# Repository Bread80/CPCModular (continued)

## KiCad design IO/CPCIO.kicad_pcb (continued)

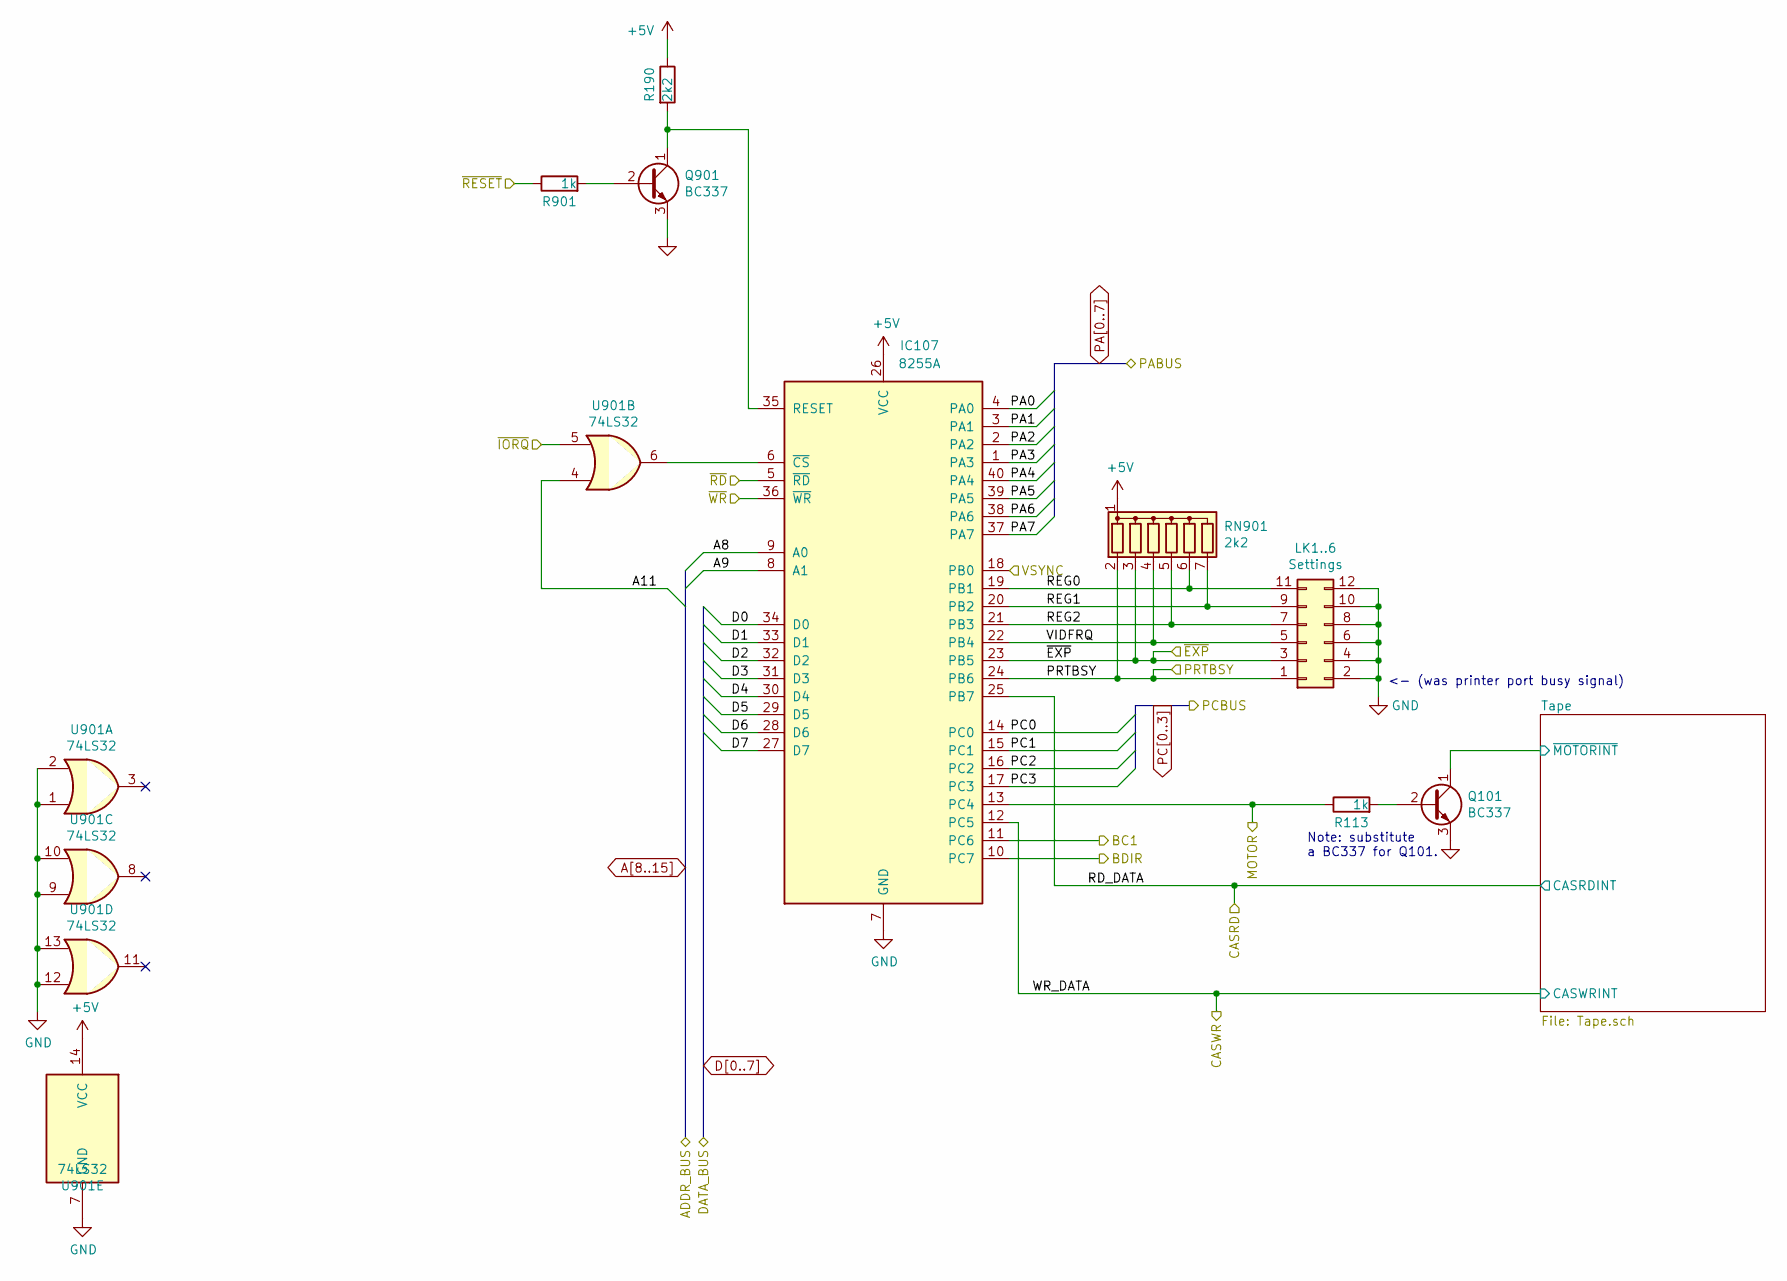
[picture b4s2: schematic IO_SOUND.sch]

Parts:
IC107: 8255A; DIP-40_W15.24mm_Socket
LK1..6: Settings; PinHeader_2x06_P2.54mm_Vertical
Q101, Q901: BC337; TO-92_HandSolder
R113, R901: 1k; R_Axial_DIN0207_L6.3mm_D2.5mm_P7.62mm_Horizontal
R190: 2k2; R_Axial_DIN0207_L6.3mm_D2.5mm_P7.62mm_Horizontal
RN901: 2k2; R_Array_SIP7
U901: 74LS32; DIP-14_W7.62mm_Socket

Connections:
+5V: IC107.26 (VCC), R190.1, RN901.1 (common), U901.14 (VCC); also elsewhere on the board
/IO_SOUND/BC1: IC107.11 (PC6); also elsewhere on the board
/IO_SOUND/BDIR: IC107.10 (PC7); also elsewhere on the board
/IO_SOUND/CASRD: IC107.25 (PB7); also elsewhere on the board
/IO_SOUND/CASWR: IC107.12 (PC5); also elsewhere on the board
/IO_SOUND/MOTOR: IC107.13 (PC4), R113.1; also elsewhere on the board
/IO_SOUND/PRTBSY: IC107.24 (PB6), LK1..6.1, RN901.2 (R1); also elsewhere on the board
/IO_SOUND/REG0: IC107.19 (PB1), LK1..6.11, RN901.6 (R5)
/IO_SOUND/REG1: IC107.20 (PB2), LK1..6.9, RN901.7 (R6)
/IO_SOUND/REG2: IC107.21 (PB3), LK1..6.7, RN901.5 (R4)
/IO_SOUND/Tape/~MOTORINT: Q101.1 (C); also elsewhere on the board
/IO_SOUND/VIDFRQ: IC107.22 (PB4), LK1..6.5, RN901.4 (R3)
/IO_SOUND/VSYNC: IC107.18 (PB0); also elsewhere on the board
/IO_SOUND/~EXP: IC107.23 (PB5), LK1..6.3, RN901.3 (R2); also elsewhere on the board
/IO_SOUND/~IORQ: U901.5; also elsewhere on the board
/IO_SOUND/~RD: IC107.5 (~RD~); also elsewhere on the board
/IO_SOUND/~RESET: R901.1; also elsewhere on the board
/IO_SOUND/~WR: IC107.36 (~WR~); also elsewhere on the board
A8: IC107.9 (A0); also elsewhere on the board
A9: IC107.8 (A1); also elsewhere on the board
A11: U901.4; also elsewhere on the board
D0: IC107.34 (D0); also elsewhere on the board
D1: IC107.33 (D1); also elsewhere on the board
D2: IC107.32 (D2); also elsewhere on the board
D3: IC107.31 (D3); also elsewhere on the board
D4: IC107.30 (D4); also elsewhere on the board
D5: IC107.29 (D5); also elsewhere on the board
D6: IC107.28 (D6); also elsewhere on the board
D7: IC107.27 (D7); also elsewhere on the board
GND: IC107.7 (GND), LK1..6.2, LK1..6.4, LK1..6.6, LK1..6.8, LK1..6.10, LK1..6.12, Q101.3 (E), Q901.3 (E), U901.1, U901.2, U901.7 (GND), U901.9, U901.10, U901.12, U901.13; also elsewhere on the board
unnamed: IC107.6 (~CS~), U901.6
unnamed: IC107.35 (RESET), Q901.1 (C), R190.2
unnamed: Q101.2 (B), R113.2
unnamed: Q901.2 (B), R901.2
PA0: IC107.4 (PA0); also elsewhere on the board
PA1: IC107.3 (PA1); also elsewhere on the board
PA2: IC107.2 (PA2); also elsewhere on the board
PA3: IC107.1 (PA3); also elsewhere on the board
PA4: IC107.40 (PA4); also elsewhere on the board
PA5: IC107.39 (PA5); also elsewhere on the board
PA6: IC107.38 (PA6); also elsewhere on the board
PA7: IC107.37 (PA7); also elsewhere on the board
PC0: IC107.14 (PC0); also elsewhere on the board
PC1: IC107.15 (PC1); also elsewhere on the board
PC2: IC107.16 (PC2); also elsewhere on the board
PC3: IC107.17 (PC3); also elsewhere on the board

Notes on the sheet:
Note: substitute a BC337 for Q101.
<- (was printer port busy signal)

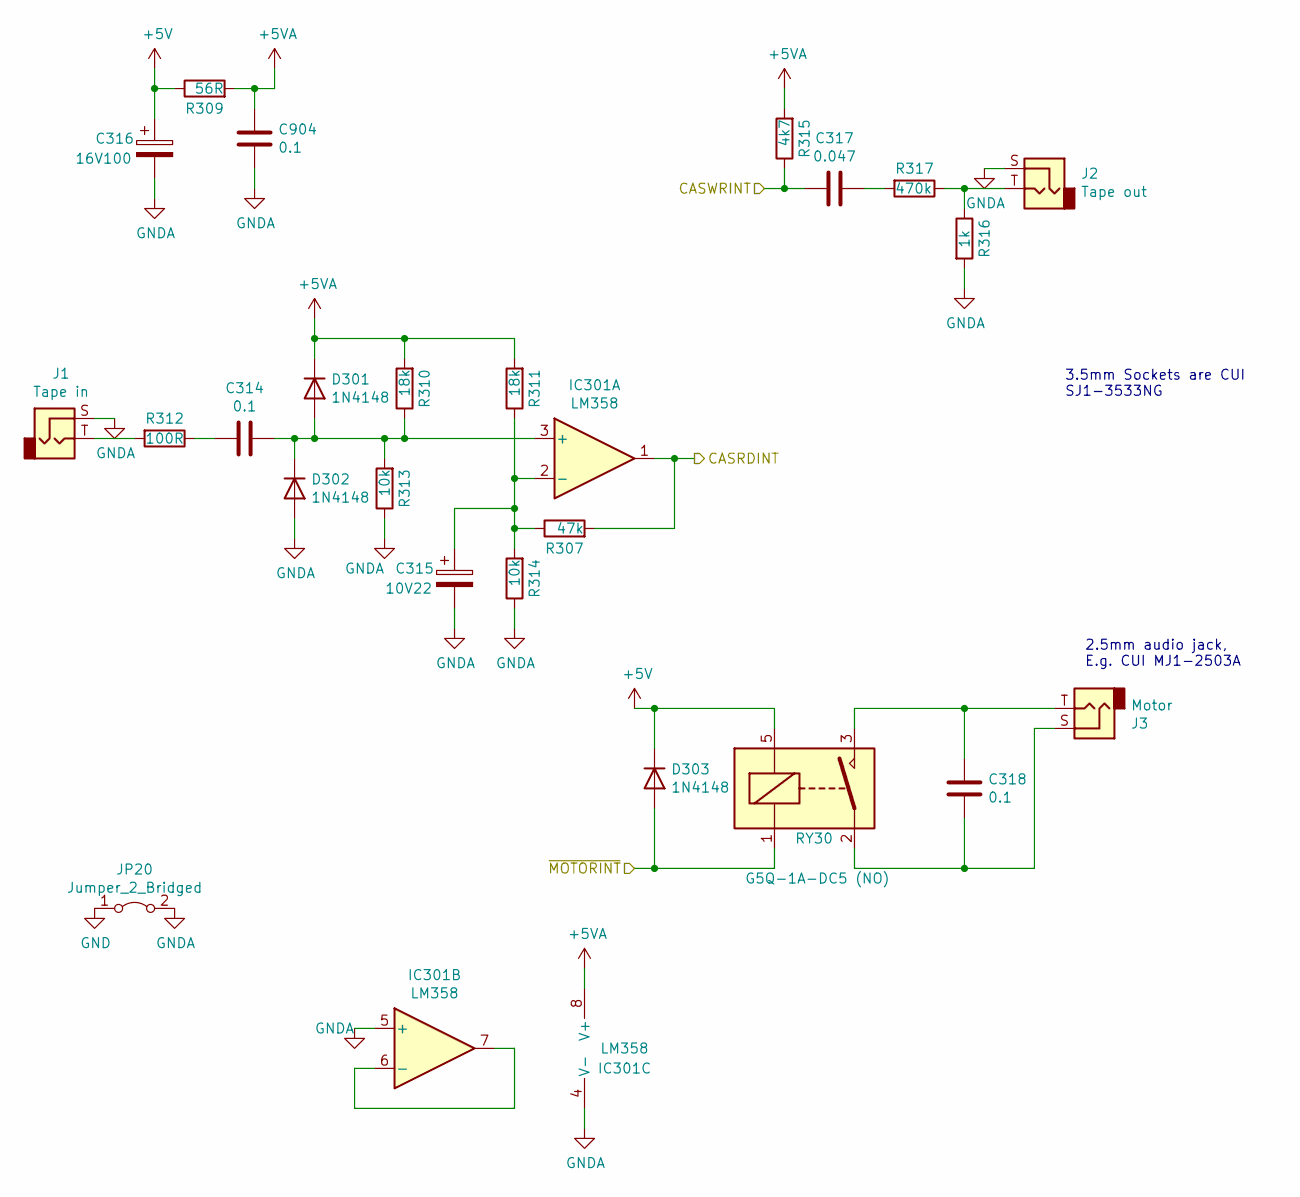
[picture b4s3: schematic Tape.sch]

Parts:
C314, C318, C904: 0.1; C_Disc_D3.0mm_W2.0mm_P2.50mm
C315: 10V22; CP_Radial_D6.3mm_P2.50mm
C316: 16V100; CP_Radial_D6.3mm_P2.50mm
C317: 0.047; C_Disc_D3.0mm_W2.0mm_P2.50mm
D301, D302, D303: 1N4148; D_DO-35_SOD27_P7.62mm_Horizontal
IC301: LM358; DIP-8_W7.62mm_Socket
J1: Tape in; Jack_3.5mm_CUI_SJ1-3533NG_Horizontal
J2: Tape out; Jack_3.5mm_CUI_SJ1-3533NG_Horizontal
J3: Motor; CUI_MJ1_2503A
JP20: Jumper_2_Bridged; NetTie-2_SMD_Pad0.5mm
R307: 47k; R_Axial_DIN0207_L6.3mm_D2.5mm_P7.62mm_Horizontal
R309: 56R; R_Axial_DIN0207_L6.3mm_D2.5mm_P7.62mm_Horizontal
R310, R311: 18k; R_Axial_DIN0207_L6.3mm_D2.5mm_P7.62mm_Horizontal
R312: 100R; R_Axial_DIN0207_L6.3mm_D2.5mm_P7.62mm_Horizontal
R313, R314: 10k; R_Axial_DIN0207_L6.3mm_D2.5mm_P7.62mm_Horizontal
R315: 4k7; R_Axial_DIN0207_L6.3mm_D2.5mm_P7.62mm_Horizontal
R316: 1k; R_Axial_DIN0207_L6.3mm_D2.5mm_P7.62mm_Horizontal
R317: 470k; R_Axial_DIN0207_L6.3mm_D2.5mm_P7.62mm_Horizontal
RY30: G5Q-1A-DC5 (NO); Relay_SPST_Omron-G5Q-1A

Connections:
+5V: C316.1, D303.1 (K), R309.1, RY30.5; also elsewhere on the board
+5VA: C904.1, D301.1 (K), IC301.8 (V+), R309.2, R310.2, R311.2, R315.2
/IO_SOUND/CASRD: IC301.1, R307.2; also elsewhere on the board
/IO_SOUND/CASWR: C317.2, R315.1; also elsewhere on the board
/IO_SOUND/Tape/~MOTORINT: D303.2 (A), RY30.1; also elsewhere on the board
GND: JP20.1 (A); also elsewhere on the board
GNDA: C315.2, C316.2, C904.2, D302.2 (A), IC301.4 (V-), IC301.5 (+), J1.S, J2.S, JP20.2 (B), R313.1, R314.1, R316.2
unnamed: C314.1, D301.2 (A), D302.1 (K), IC301.3 (+), R310.1, R313.2
unnamed: C314.2, R312.1
unnamed: C315.1, IC301.2 (-), R307.1, R311.1, R314.2
unnamed: C317.1, R317.2
unnamed: C318.1, J3.T, RY30.3
unnamed: C318.2, J3.S, RY30.2
unnamed: IC301.6 (-), IC301.7
unnamed: J1.T, R312.2
unnamed: J2.T, R316.1, R317.1

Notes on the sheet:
3.5mm Sockets are CUI SJ1-3533NG
2.5mm audio jack, E.g. CUI MJ1-2503A

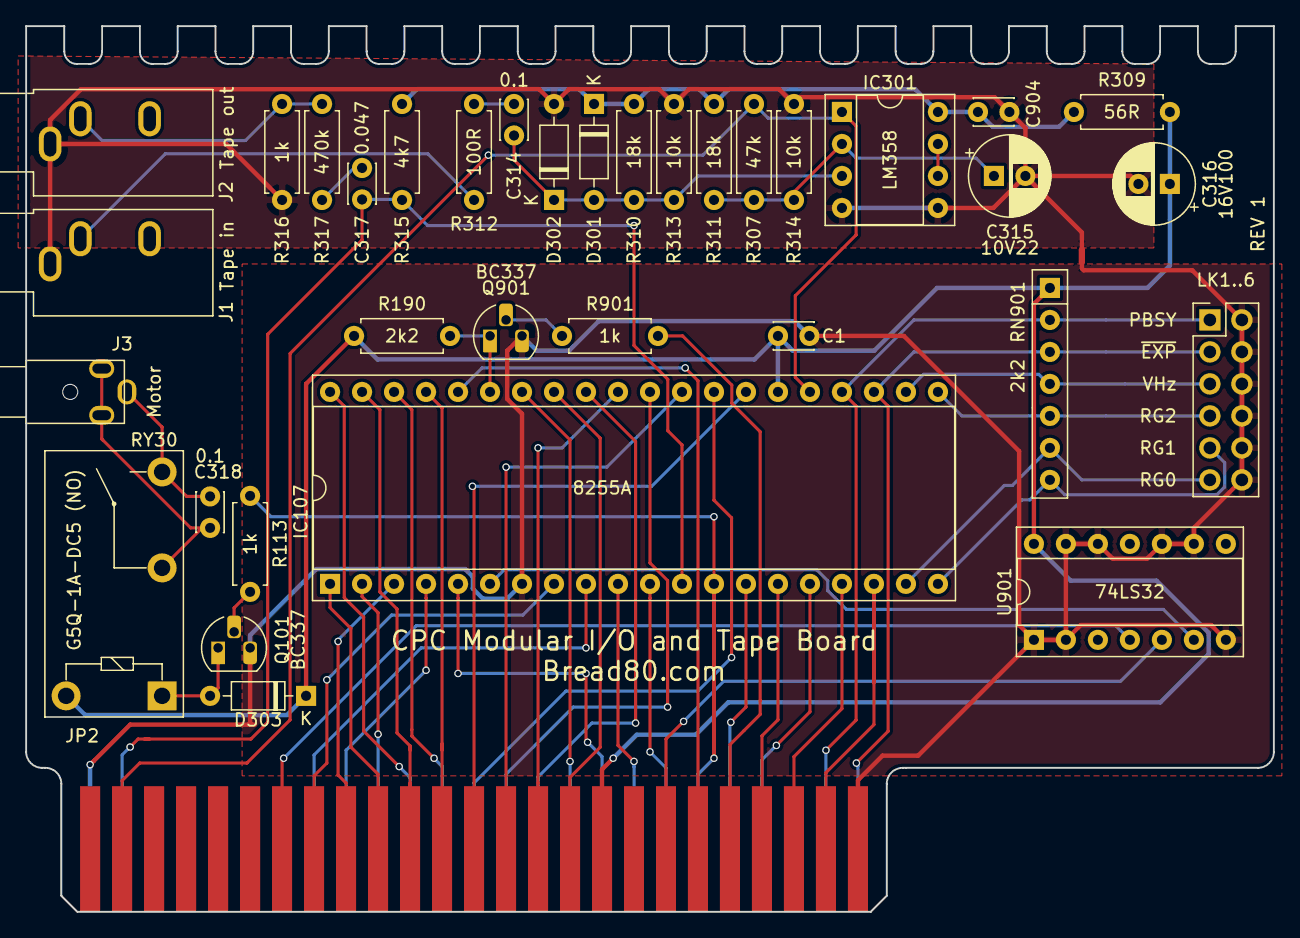
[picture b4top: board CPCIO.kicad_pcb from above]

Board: 2 copper layers, 99.1 x 70.3 mm, 37 parts (1 on the bottom side), 57 nets.

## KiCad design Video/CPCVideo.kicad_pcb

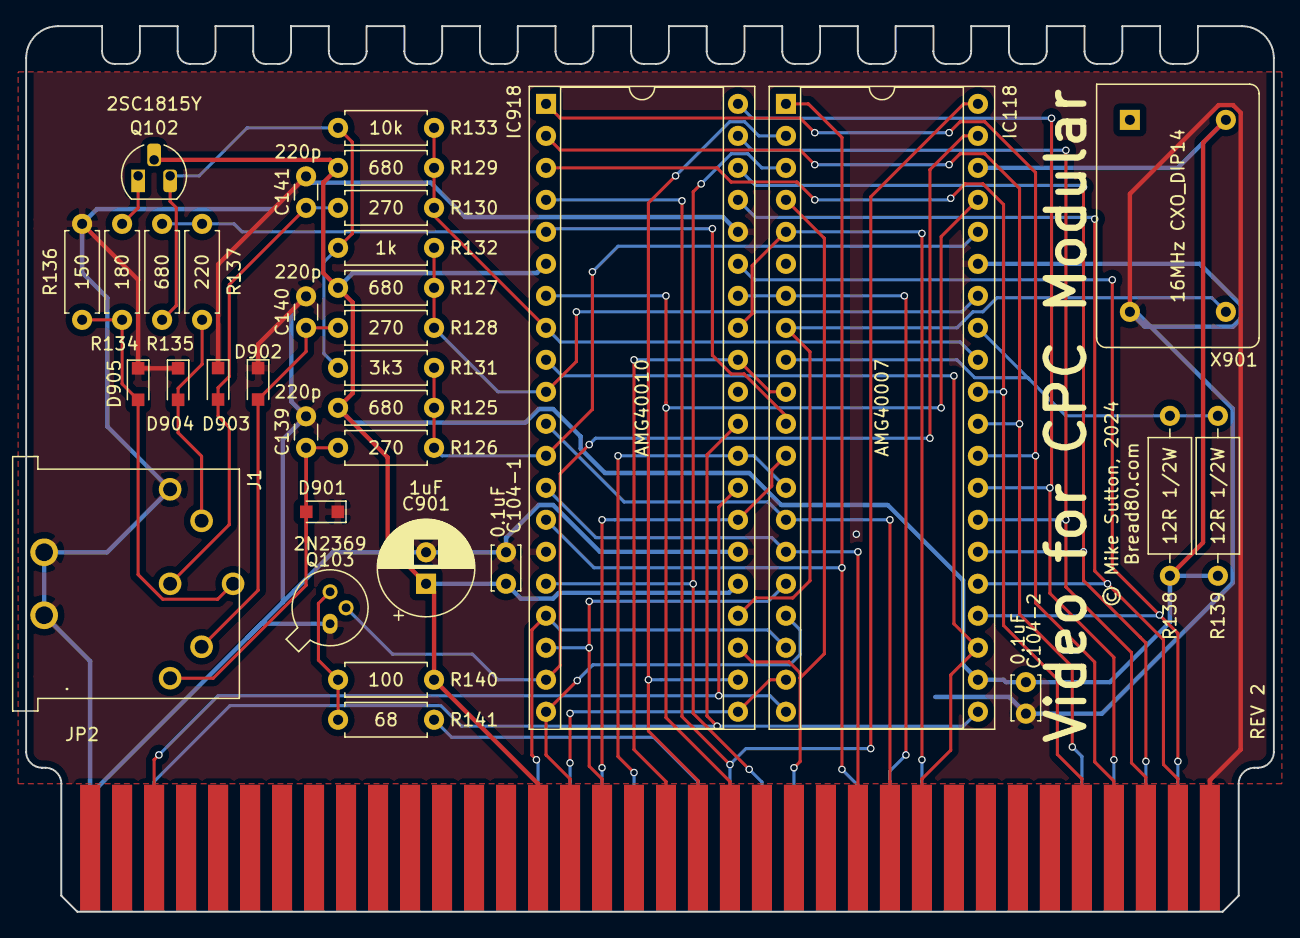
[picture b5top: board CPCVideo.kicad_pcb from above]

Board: 2 copper layers, 99.1 x 70.3 mm, 36 parts (1 on the bottom side), 46 nets.

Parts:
C104-1, C104-2: 0.1uF; C_Disc_D3.4mm_W2.1mm_P2.50mm
C139, C140, C141: 220p; C_Disc_D3.0mm_W1.6mm_P2.50mm
C901: 1uF; CP_Radial_D7.5mm_P2.50mm
D901, D902, D903, D904, D905: PESD5V0V1BA; D_SOD-323_HandSoldering
IC118: AMG40007; DIP-40_W15.24mm_Socket
IC918: AMG40010; DIP-40_W15.24mm_Socket
J1: VIDEO OUT; 6PinDIN240Degree
JP1: CPCM_VideoRAM_EdgeBottom; Edge36_2.54PS
JP2: CPCM_VideoRAM_EdgeTop; Edge36_2.54PS
Q102: 2SC1815Y; TO-92_HandSolder
Q103: 2N2369; TO-18-3
R125, R127, R129, R135: 680; R_Axial_DIN0207_L6.3mm_D2.5mm_P7.62mm_Horizontal
R126, R128, R130: 270; R_Axial_DIN0207_L6.3mm_D2.5mm_P7.62mm_Horizontal
R131: 3k3; R_Axial_DIN0207_L6.3mm_D2.5mm_P7.62mm_Horizontal
R132: 1k; R_Axial_DIN0207_L6.3mm_D2.5mm_P7.62mm_Horizontal
R133: 10k; R_Axial_DIN0207_L6.3mm_D2.5mm_P7.62mm_Horizontal
R134: 180; R_Axial_DIN0207_L6.3mm_D2.5mm_P7.62mm_Horizontal
R136: 150; R_Axial_DIN0207_L6.3mm_D2.5mm_P7.62mm_Horizontal
R137: 220; R_Axial_DIN0207_L6.3mm_D2.5mm_P7.62mm_Horizontal
R138, R139: 12R 1/2W; R_Axial_DIN0309_L9.0mm_D3.2mm_P12.70mm_Horizontal
R140: 100; R_Axial_DIN0207_L6.3mm_D2.5mm_P7.62mm_Horizontal
R141: 68; R_Axial_DIN0207_L6.3mm_D2.5mm_P7.62mm_Horizontal
X901: 16MHz CXO_DIP14; Oscillator_DIP-14

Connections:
+5V: C104-1.1, C104-2.1, C901.1, IC118.22, IC118.38, IC918.6, IC918.25, JP2.15, Q102.2, R125.2, R127.2, R129.2, R138.1, R139.1, R140.2, X901.14
/RAM_GA/BLUE: C141.1, D903.2, J1.3, R130.2
/RAM_GA/DISPEN: IC118.23, IC918.9, JP2.27
/RAM_GA/GREEN: C140.1, D902.2, J1.2, R128.2
/RAM_GA/GateArrays/B: IC118.32, IC918.8, R129.1, R130.1, R133.2
/RAM_GA/GateArrays/G: IC118.34, IC918.10, R127.1, R128.1, R132.2
/RAM_GA/GateArrays/PHI: IC118.39, IC918.19, Q103.2
/RAM_GA/GateArrays/R: IC118.36, IC918.12, R125.1, R126.1, R131.2
/RAM_GA/GateArrays/XTAL: IC118.8, IC918.24, X901.8
/RAM_GA/GateArrays/~SYNC: IC118.11, IC918.5, R135.1, R137.1
/RAM_GA/HSYNC: IC118.14, IC918.11, JP2.26
/RAM_GA/LUM: D905.2, J1.6, R134.2, R136.1
/RAM_GA/MA0_CCLK: IC118.40, IC918.4, JP1.21
/RAM_GA/PHI: JP1.20, R141.2
/RAM_GA/READY: IC118.2, IC918.22, JP2.20
/RAM_GA/RED: C139.1, D901.2, J1.1, R126.2
/RAM_GA/VSYNC: IC118.15, IC918.13, JP2.25
/RAM_GA/~244EN: IC118.4, IC918.23, JP1.23
/RAM_GA/~CAS: IC118.3, IC918.16, JP1.22
/RAM_GA/~CPU_ADDR: IC118.1, IC918.14, JP1.25
/RAM_GA/~INT: IC118.10, IC918.32, JP2.19
/RAM_GA/~IORQ: IC118.16, IC918.18, JP2.17
/RAM_GA/~M1: IC118.17, IC918.20, JP2.16
/RAM_GA/~MREQ: IC118.18, IC918.17, JP1.15
/RAM_GA/~MWE: IC118.5, IC918.33, JP1.27
/RAM_GA/~RAMRD: IC118.13, IC918.29, JP1.18
/RAM_GA/~RAS: IC118.7, IC918.34, JP1.26
/RAM_GA/~RD: IC118.19, IC918.21, JP1.16
/RAM_GA/~RESET: IC118.37, IC918.7, JP2.21
/RAM_GA/~ROMEN: IC118.12, IC918.27, JP1.17
/RAM_GA/~SYNC: D904.2, J1.4, R137.2
A14: IC118.21, IC918.30, JP1.3
A15: IC118.20, IC918.28, JP2.3
GND: C104-1.2, C104-2.2, C139.2, C140.2, C141.2, C901.2, D901.1, D902.1, D903.1, D904.1, D905.1, IC118.35, IC918.15, IC918.26, IC918.36, J1.5, J1.SH, JP1.1, JP2.36, Q103.1, R136.2, X901.7
unnamed: IC118.9, IC118.33, R138.2, R139.2
unnamed: Q102.1, R134.1
unnamed: Q102.3, R131.1, R132.1, R133.1, R135.2
unnamed: Q103.3, R140.1, R141.1
RD0: IC118.24, IC918.35, JP1.35
RD1: IC118.25, IC918.37, JP2.35
RD2: IC118.26, IC918.38, JP1.34
RD3: IC118.27, IC918.39, JP2.34
RD4: IC118.28, IC918.40, JP1.33
RD5: IC118.29, IC918.1, JP2.33
RD6: IC118.30, IC918.2, JP1.32
RD7: IC118.31, IC918.3, JP2.32

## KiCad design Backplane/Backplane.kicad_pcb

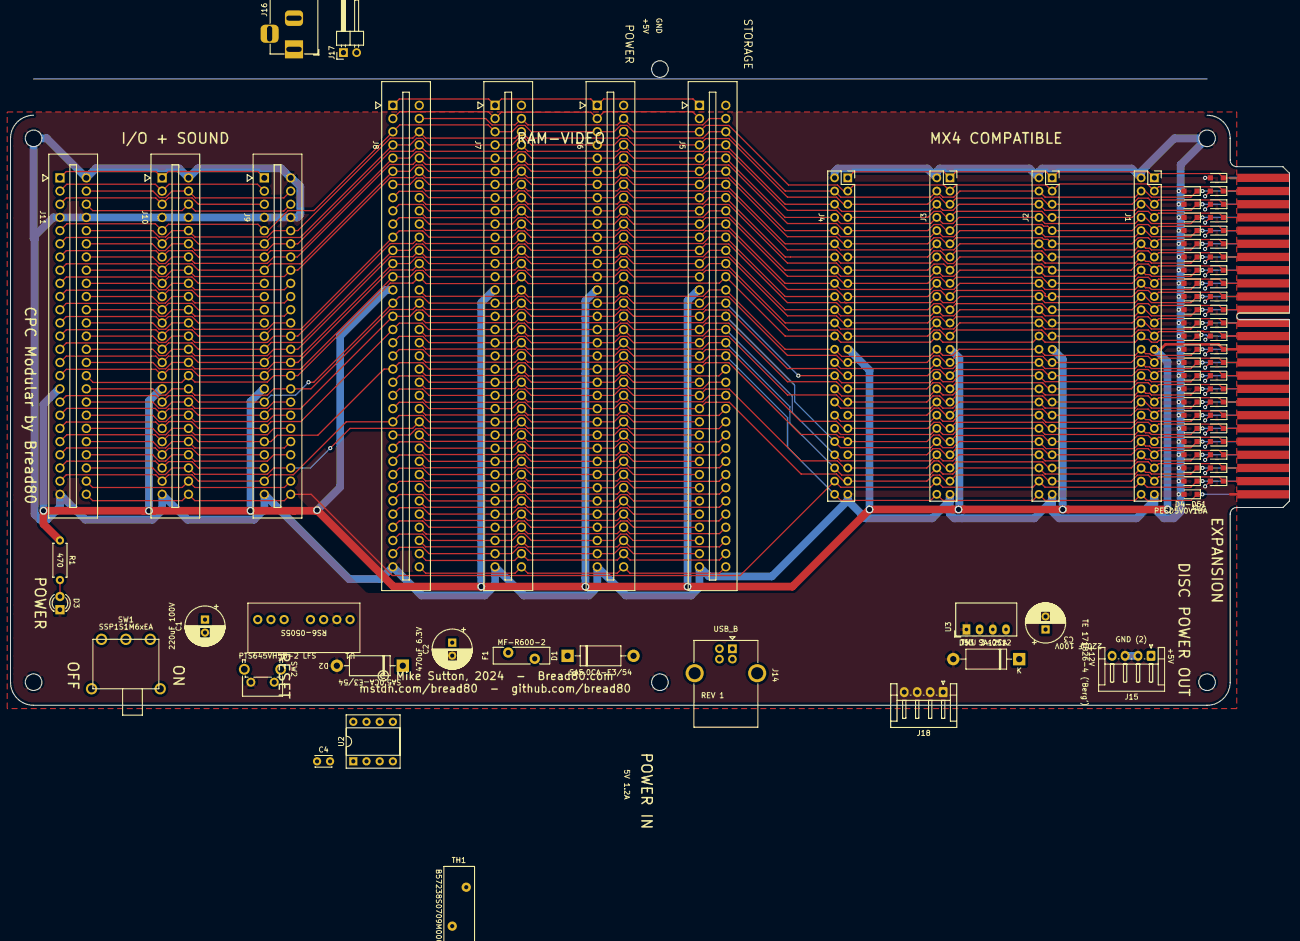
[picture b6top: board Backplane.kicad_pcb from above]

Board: 2 copper layers, 246.4 x 120.7 mm, 88 parts (1 on the bottom side), 107 nets.

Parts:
C1, C3: 220uF 100V; CP_Radial_D7.5mm_P2.50mm
C2: 470uF 6.3V; CP_Radial_D7.5mm_P2.50mm
C4: 0.1uF; C_Disc_D3.0mm_W2.0mm_P2.50mm
D1, D2: SA5.0CA-E3/54; D_DO-15_P12.70mm_Horizontal
D3: POWER; LED_D3.0mm
D4, D5, D6, D7, D8, D9, D10, D11, D12, D13, D14, D15, D16, D17, D18, D19, D20, D21, D22, D23, D24, D25, D26, D27, D28, D29, D30, D31, D32, D33, D34, D35, D36, D37, D38, D39, D40, D41, D42, D43, D44, D45, D46, D47, D48, D49, D50, D51: PESD5V0V1BA; D_SOD-323_HandSoldering
D53: SA12CA; D_DO-15_P12.70mm_Horizontal
F1: MF-R600-2; Fuse_Bourns_MF-RG600
H1, H2, H3, H4, H5, H6: MountingHole_Pad; MountingHole_3.2mm_M3
J1, J2, J3, J4: Conn_02x25_Odd_Even; PinSocket_2x25_P2.54mm_Vertical
J5, J6, J7, J8: Conn_02x36_Top_Bottom; Edge_Socket_2x36_2.54PS
J9, J10, J11: Conn_02x25_Top_Bottom; Edge_Socket_2x25_2.54PS
J12: Expansion Top (Edge connector); Edge25_2.54PS
J13: Expansion Bottom (Edge connector); Edge25_2.54PS
J14: USB_B; USB_B_OST_USB-B1HSxx_Horizontal
J15: TE 171826-4 ('Berg'); JST_EH_S4B-EH_1x04_P2.50mm_Horizontal
J16: Barrel_Jack_MountingPin; BarrelJack_Horizontal
J17: SCART POWER; PinHeader_1x02_P2.54mm_Horizontal
J18: TE 770997-1 ('Molex'); JST_EH_S4B-EH_1x04_P2.50mm_Horizontal
R1: 470; R_Axial_DIN0207_L6.3mm_D2.5mm_P7.62mm_Horizontal
SW1: SSP1S1M6xEA; E-Switch_SSP1_M6_A
SW2: PTS645VH58-2 LFS; SW_Tactile_SPST_Angled_PTS645Vx58-2LFS
TH1: B57238S0709M000; RV_Disc_D15.5mm_W5.9mm_P7.5mm
U1: RS6-0505S; Recom_RS6_Series_SIP8
U2: ADM708 or MAX708; DIP-8_W7.62mm_Socket
U3: TMU 3-0512; Converter_DCDC_muRata_CRE1xxxxxxSC_THT

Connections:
+5V: C2.1, C4.1, D2.1, D17.1, J1.27, J2.27, J3.27, J4.27, J5.15, J6.15, J7.15, J8.15, J9.17, J10.17, J11.17, J12.14, J15.1, J17.2, R1.1, U1.6, U2.2
+12V: C3.1, D53.1, J15.4, U3.4
/A0: D35.1, J1.18, J2.18, J3.18, J4.18, J5.46, J6.46, J7.46, J8.46, J13.9
/A1: D12.1, J1.17, J2.17, J3.17, J4.17, J5.10, J6.10, J7.10, J8.10, J12.9
/A2: D34.1, J1.16, J2.16, J3.16, J4.16, J5.45, J6.45, J7.45, J8.45, J13.8
/A3: D11.1, J1.15, J2.15, J3.15, J4.15, J5.9, J6.9, J7.9, J8.9, J12.8
/A4: D33.1, J1.14, J2.14, J3.14, J4.14, J5.44, J6.44, J7.44, J8.44, J13.7
/A5: D10.1, J1.13, J2.13, J3.13, J4.13, J5.8, J6.8, J7.8, J8.8, J12.7
/A6: D32.1, J1.12, J2.12, J3.12, J4.12, J5.43, J6.43, J7.43, J8.43, J13.6
/A7: D9.1, J1.11, J2.11, J3.11, J4.11, J5.7, J6.7, J7.7, J8.7, J12.6
/A8: D31.1, J1.10, J2.10, J3.10, J4.10, J5.42, J6.42, J7.42, J8.42, J9.33, J10.33, J11.33, J13.5
/A9: D8.1, J1.9, J2.9, J3.9, J4.9, J5.6, J6.6, J7.6, J8.6, J9.8, J10.8, J11.8, J12.5
/A10: D30.1, J1.8, J2.8, J3.8, J4.8, J5.41, J6.41, J7.41, J8.41, J9.32, J10.32, J11.32, J13.4
/A11: D7.1, J1.7, J2.7, J3.7, J4.7, J5.5, J6.5, J7.5, J8.5, J9.7, J10.7, J11.7, J12.4
/A12: D29.1, J1.6, J2.6, J3.6, J4.6, J5.40, J6.40, J7.40, J8.40, J9.31, J10.31, J11.31, J13.3
/A13: D6.1, J1.5, J2.5, J3.5, J4.5, J5.4, J6.4, J7.4, J8.4, J9.6, J10.6, J11.6, J12.3
/A14: D28.1, J1.4, J2.4, J3.4, J4.4, J5.39, J6.39, J7.39, J8.39, J9.30, J10.30, J11.30, J13.2
/A14OUT: J5.38, J6.38, J7.38, J8.38
/A15: D5.1, J1.3, J2.3, J3.3, J4.3, J5.3, J6.3, J7.3, J8.3, J9.5, J10.5, J11.5, J12.2
/A15OUT: J5.2, J6.2, J7.2, J8.2
/BC1: J9.44, J10.44, J11.44
/BDIR: J9.43, J10.43, J11.43
/CASRD: J9.2, J10.2, J11.2
/CASWR: J9.27, J10.27, J11.27
/CLK4: D51.1, J1.50, J2.50, J3.50, J4.50, J5.56, J6.56, J7.56, J8.56, J13.25
/CURSOR: D49.1, J1.46, J2.46, J3.46, J4.46, J5.55, J6.55, J7.55, J8.55, J13.23
/D0: D39.1, J1.26, J2.26, J3.26, J4.26, J5.50, J6.50, J7.50, J8.50, J9.41, J10.41, J11.41, J13.13
/D1: D16.1, J1.25, J2.25, J3.25, J4.25, J5.14, J6.14, J7.14, J8.14, J9.16, J10.16, J11.16, J12.13
/D2: D38.1, J1.24, J2.24, J3.24, J4.24, J5.49, J6.49, J7.49, J8.49, J9.40, J10.40, J11.40, J13.12
/D3: D15.1, J1.23, J2.23, J3.23, J4.23, J5.13, J6.13, J7.13, J8.13, J9.15, J10.15, J11.15, J12.12
/D4: D37.1, J1.22, J2.22, J3.22, J4.22, J5.48, J6.48, J7.48, J8.48, J9.39, J10.39, J11.39, J13.11
/D5: D14.1, J1.21, J2.21, J3.21, J4.21, J5.12, J6.12, J7.12, J8.12, J9.14, J10.14, J11.14, J12.11
/D6: D36.1, J1.20, J2.20, J3.20, J4.20, J5.47, J6.47, J7.47, J8.47, J9.38, J10.38, J11.38, J13.10
/D7: D13.1, J1.19, J2.19, J3.19, J4.19, J5.11, J6.11, J7.11, J8.11, J9.13, J10.13, J11.13, J12.10
/DISPEN: J5.27, J6.27, J7.27, J8.27
/HSYNC: J5.26, J6.26, J7.26, J8.26
/LEFT: J9.3, J10.3, J11.3
/LPEN: D27.1, J1.47, J2.47, J3.47, J4.47, J5.24, J6.24, J7.24, J8.24, J12.24
/MOTOR: J9.45, J10.45, J11.45
/PA0: J9.34, J10.34, J11.34
/PA1: J9.9, J10.9, J11.9
/PA2: J9.35, J10.35, J11.35
/PA3: J9.10, J10.10, J11.10
/PA4: J9.36, J10.36, J11.36
/PA5: J9.11, J10.11, J11.11
/PA6: J9.37, J10.37, J11.37
/PA7: J9.12, J10.12, J11.12
/PC0: J9.46, J10.46, J11.46
/PC1: J9.22, J10.22, J11.22
/PC2: J9.47, J10.47, J11.47
/PC3: J9.23, J10.23, J11.23
/PRTBSY: J9.49, J10.49, J11.49
/RAMA16: J5.66, J6.66, J7.66, J8.66
/RAMA17: J5.30, J6.30, J7.30, J8.30
/RAMA18: J5.65, J6.65, J7.65, J8.65
/RAMDIS: D26.1, J1.45, J2.45, J3.45, J4.45, J5.23, J6.23, J7.23, J8.23, J12.23
/RD0: J5.71, J6.71, J7.71, J8.71
/RD1: J5.35, J6.35, J7.35, J8.35
/RD2: J5.70, J6.70, J7.70, J8.70
/RD3: J5.34, J6.34, J7.34, J8.34
/RD4: J5.69, J6.69, J7.69, J8.69
/RD5: J5.33, J6.33, J7.33, J8.33
/RD6: J5.68, J6.68, J7.68, J8.68
/RD7: J5.32, J6.32, J7.32, J8.32
/READY: D23.1, J1.39, J2.39, J3.39, J4.39, J5.20, J6.20, J7.20, J8.20, J12.20
/RIGHT: J9.28, J10.28, J11.28
/ROMDIS: D25.1, J1.43, J2.43, J3.43, J4.43, J12.22
/SOUND: D4.1, J1.1, J2.1, J3.1, J4.1, J9.1, J10.1, J11.1, J12.1
/SPARE1: J5.1, J6.1, J7.1, J8.1
/SPARE2: J5.22, J6.22, J7.22, J8.22
/SPARE3: J5.31, J6.31, J7.31, J8.31
/SPARE4: J5.67, J6.67, J7.67, J8.67
/SPARE5: J5.72, J6.72, J7.72, J8.72
/SWITCHED_5V: C1.1, SW1.1, U1.2, U2.4, U3.2
/UGND: C1.2, D1.2, J14.4, J14.5, U1.1
/VBUS: F1.2, J14.1
/VSYNC: J5.25, J6.25, J7.25, J8.25, J9.24, J10.24, J11.24
/~244EN: J5.59, J6.59, J7.59, J8.59
/~BRST: D46.1, J1.40, J2.40, J3.40, J4.40, J13.20, SW2.1, U2.1
/~BUSAK: D45.1, J1.38, J2.38, J3.38, J4.38, J13.19
/~BUSRQ: D22.1, J1.37, J2.37, J3.37, J4.37, J12.19
/~CAS: J5.58, J6.58, J7.58, J8.58
/~CPU_ADDR: J5.61, J6.61, J7.61, J8.61, J9.48, J10.48, J11.48
/~EXP: D50.1, J1.48, J2.48, J3.48, J4.48, J9.50, J10.50, J11.50, J13.24
/~HALT: D43.1, J1.34, J2.34, J3.34, J4.34, J13.17
/~INT: D21.1, J1.35, J2.35, J3.35, J4.35, J5.19, J6.19, J7.19, J8.19, J12.18
/~IORQ: D19.1, J1.31, J2.31, J3.31, J4.31, J5.17, J6.17, J7.17, J8.17, J9.19, J10.19, J11.19, J12.16
/~M1: D18.1, J1.29, J2.29, J3.29, J4.29, J5.16, J6.16, J7.16, J8.16, J9.18, J10.18, J11.18, J12.15
/~MA0_CCLK: J5.57, J6.57, J7.57, J8.57
/~MREQ: D40.1, J1.28, J2.28, J3.28, J4.28, J5.51, J6.51, J7.51, J8.51, J13.14
/~MWE: J5.63, J6.63, J7.63, J8.63
/~NMI: D44.1, J1.36, J2.36, J3.36, J4.36, J13.18
/~RAMCS: J5.64, J6.64, J7.64, J8.64
/~RAMOE: J5.28, J6.28, J7.28, J8.28
/~RAMRD: D48.1, J1.44, J2.44, J3.44, J4.44, J5.54, J6.54, J7.54, J8.54, J13.22
/~RAMWE: J5.29, J6.29, J7.29, J8.29
/~RAS: J5.62, J6.62, J7.62, J8.62
/~RD: D42.1, J1.32, J2.32, J3.32, J4.32, J5.52, J6.52, J7.52, J8.52, J9.42, J10.42, J11.42, J13.16
/~RFSH: D41.1, J1.30, J2.30, J3.30, J4.30, J13.15
/~ROMEN: D47.1, J1.42, J2.42, J3.42, J4.42, J5.53, J6.53, J7.53, J8.53, J13.21
/~RSET: D24.1, J1.41, J2.41, J3.41, J4.41, J5.21, J6.21, J7.21, J8.21, J9.21, J10.21, J11.21, J12.21, U2.7
/~WR: D20.1, J1.33, J2.33, J3.33, J4.33, J5.18, J6.18, J7.18, J8.18, J9.20, J10.20, J11.20, J12.17
/~XCPU_AD: J5.60, J6.60, J7.60, J8.60
GND: C2.2, C3.2, C4.2, D2.2, D3.1, D4.2, D5.2, D6.2, D7.2, D8.2, D9.2, D10.2, D11.2, D12.2, D13.2, D14.2, D15.2, D16.2, D17.2, D18.2, D19.2, D20.2, D21.2, D22.2, D23.2, D24.2, D25.2, D26.2, D27.2, D28.2, D29.2, D30.2, D31.2, D32.2, D33.2, D34.2, D35.2, D36.2, D37.2, D38.2, D39.2, D40.2, D41.2, D42.2, D43.2, D44.2, D45.2, D46.2, D47.2, D48.2, D49.2, D50.2, D51.2, D53.2, H1.1, H2.1, H3.1, H4.1, H5.1, H6.1, J1.2, J1.49, J2.2, J2.49, J3.2, J3.49, J4.2, J4.49, J5.36, J5.37, J6.36, J6.37, J7.36, J7.37, J8.36, J8.37, J9.4, J9.25, J9.26, J9.29, J10.4, J10.25, J10.26, J10.29, J11.4, J11.25, J11.26, J11.29, J12.25, J13.1, J15.2, J15.3, J17.1, SW2.2, U1.7, U2.3, U3.1, U3.3
unnamed: D1.1, F1.1, TH1.2
unnamed: D3.2, R1.2
unnamed: SW1.2, TH1.1

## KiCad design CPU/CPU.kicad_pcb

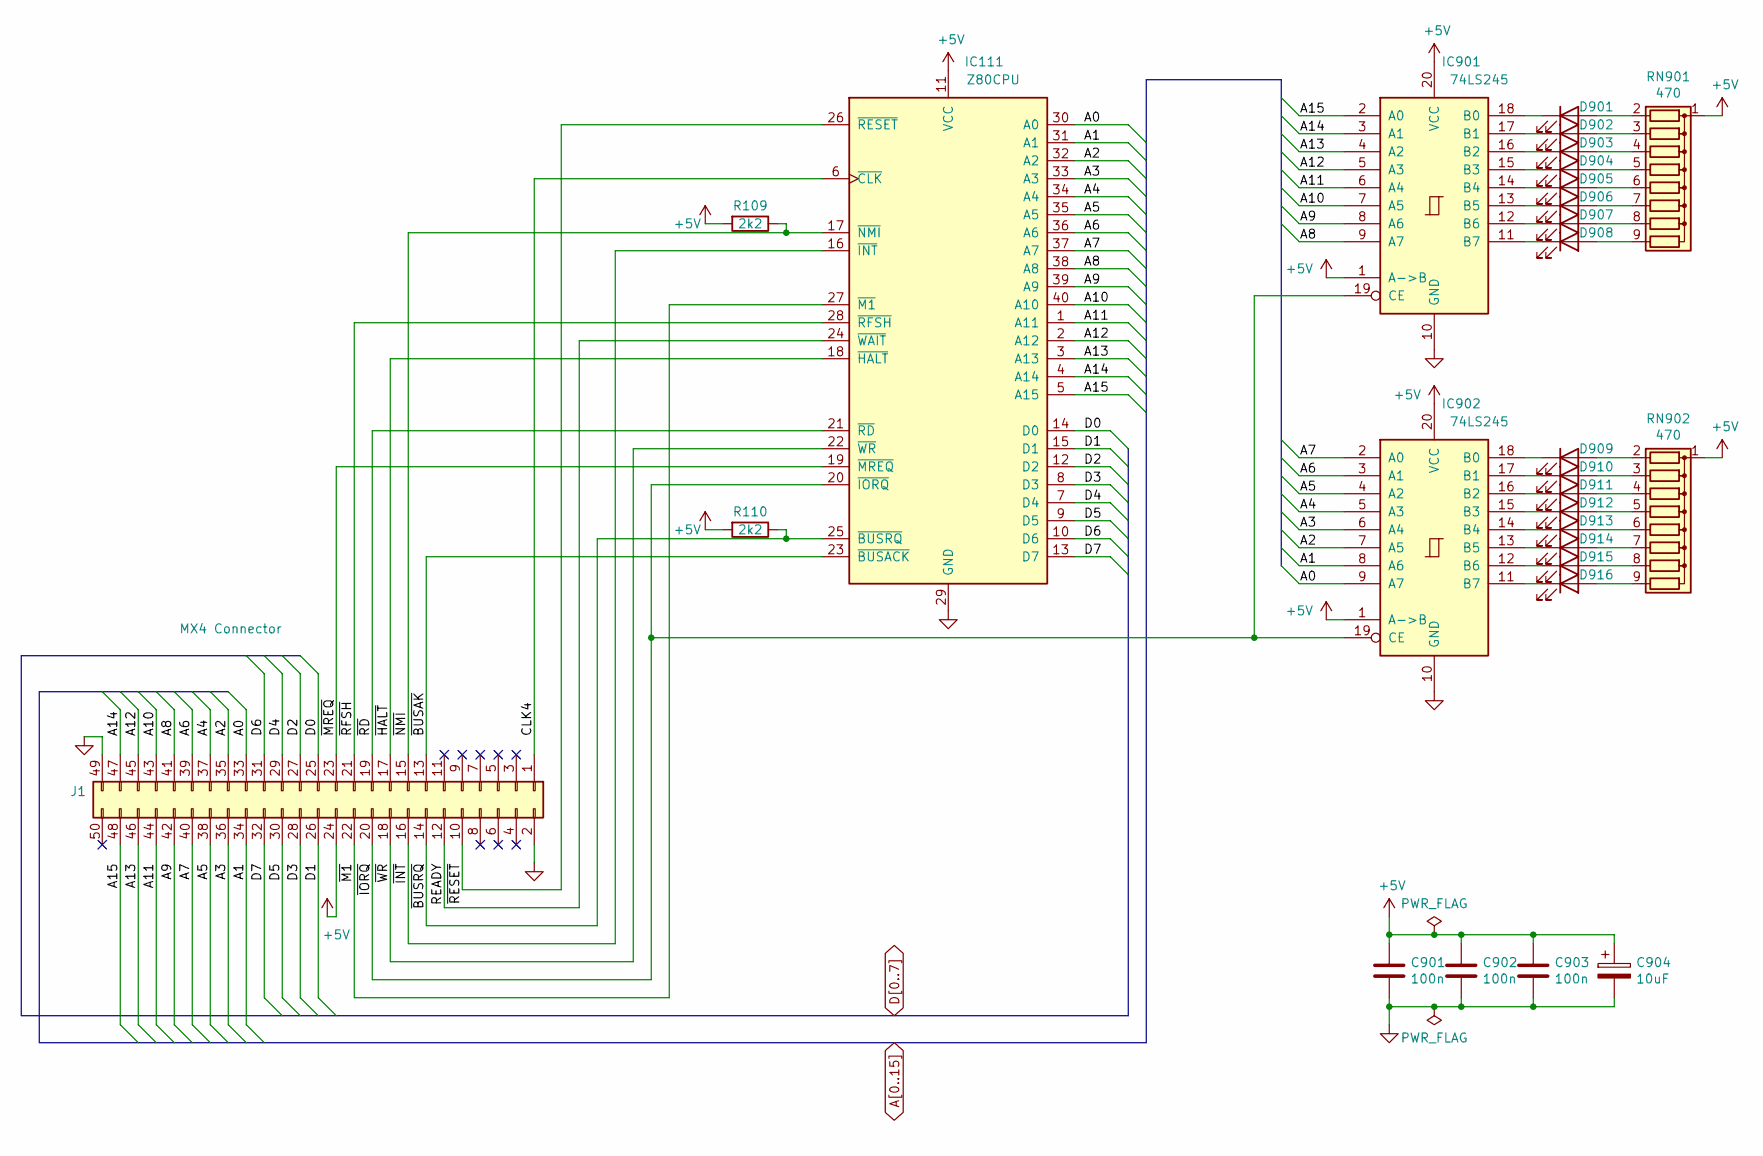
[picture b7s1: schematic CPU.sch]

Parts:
C901, C902, C903: 100n; C_Rect_L4.6mm_W2.0mm_P2.50mm_MKS02_FKP02
C904: 10uF; CP_Radial_D5.0mm_P2.00mm
D901, D902, D903, D904, D905, D906, D907, D908, D909, D910, D911, D912, D913, D914, D915, D916: LED; LED_D3.0mm
IC111: Z80CPU; DIP-40_W15.24mm_Socket
IC901, IC902: 74LS245; DIP-20_W7.62mm_Socket
J1: MX4 Connector; IDC-Header_2x25_P2.54mm_Horizontal
R109, R110: 2k2; R_Axial_DIN0207_L6.3mm_D2.5mm_P7.62mm_Horizontal
RN901, RN902: 470; R_Array_SIP9

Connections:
+5V: C901.1, C902.1, C903.1, C904.1, IC111.11 (VCC), IC901.1 (A->B), IC901.20 (VCC), IC902.1 (A->B), IC902.20 (VCC), J1.24, R109.2, R110.2, RN901.1 (common), RN902.1 (common)
/CLK4: IC111.6 (~CLK~), J1.1
/READY: IC111.24 (~WAIT~), J1.12
/~BUSAK: IC111.23 (~BUSACK~), J1.13
/~BUSRQ: IC111.25 (~BUSRQ~), J1.14, R110.1
/~HALT: IC111.18 (~HALT~), J1.17
/~INT: IC111.16 (~INT~), J1.16
/~IORQ: IC111.20 (~IORQ~), IC901.19 (CE), IC902.19 (CE), J1.20
/~M1: IC111.27 (~M1~), J1.22
/~MREQ: IC111.19 (~MREQ~), J1.23
/~NMI: IC111.17 (~NMI~), J1.15, R109.1
/~RD: IC111.21 (~RD~), J1.19
/~RESET: IC111.26 (~RESET~), J1.10
/~RFSH: IC111.28 (~RFSH~), J1.21
/~WR: IC111.22 (~WR~), J1.18
A0: IC111.30 (A0), IC902.9 (A7), J1.33
A1: IC111.31 (A1), IC902.8 (A6), J1.34
A2: IC111.32 (A2), IC902.7 (A5), J1.35
A3: IC111.33 (A3), IC902.6 (A4), J1.36
A4: IC111.34 (A4), IC902.5 (A3), J1.37
A5: IC111.35 (A5), IC902.4 (A2), J1.38
A6: IC111.36 (A6), IC902.3 (A1), J1.39
A7: IC111.37 (A7), IC902.2 (A0), J1.40
A8: IC111.38 (A8), IC901.9 (A7), J1.41
A9: IC111.39 (A9), IC901.8 (A6), J1.42
A10: IC111.40 (A10), IC901.7 (A5), J1.43
A11: IC111.1 (A11), IC901.6 (A4), J1.44
A12: IC111.2 (A12), IC901.5 (A3), J1.45
A13: IC111.3 (A13), IC901.4 (A2), J1.46
A14: IC111.4 (A14), IC901.3 (A1), J1.47
A15: IC111.5 (A15), IC901.2 (A0), J1.48
D0: IC111.14 (D0), J1.25
D1: IC111.15 (D1), J1.26
D2: IC111.12 (D2), J1.27
D3: IC111.8 (D3), J1.28
D4: IC111.7 (D4), J1.29
D5: IC111.9 (D5), J1.30
D6: IC111.10 (D6), J1.31
D7: IC111.13 (D7), J1.32
GND: C901.2, C902.2, C903.2, C904.2, IC111.29 (GND), IC901.10 (GND), IC902.10 (GND), J1.2, J1.49
unnamed: D901.1 (K), IC901.18 (B0)
unnamed: D901.2 (A), RN901.2 (R1)
unnamed: D902.1 (K), IC901.17 (B1)
unnamed: D902.2 (A), RN901.3 (R2)
unnamed: D903.1 (K), IC901.16 (B2)
unnamed: D903.2 (A), RN901.4 (R3)
unnamed: D904.1 (K), IC901.15 (B3)
unnamed: D904.2 (A), RN901.5 (R4)
unnamed: D905.1 (K), IC901.14 (B4)
unnamed: D905.2 (A), RN901.6 (R5)
unnamed: D906.1 (K), IC901.13 (B5)
unnamed: D906.2 (A), RN901.7 (R6)
unnamed: D907.1 (K), IC901.12 (B6)
unnamed: D907.2 (A), RN901.8 (R7)
unnamed: D908.1 (K), IC901.11 (B7)
unnamed: D908.2 (A), RN901.9 (R8)
unnamed: D909.1 (K), IC902.18 (B0)
unnamed: D909.2 (A), RN902.2 (R1)
unnamed: D910.1 (K), IC902.17 (B1)
unnamed: D910.2 (A), RN902.3 (R2)
unnamed: D911.1 (K), IC902.16 (B2)
unnamed: D911.2 (A), RN902.4 (R3)
unnamed: D912.1 (K), IC902.15 (B3)
unnamed: D912.2 (A), RN902.5 (R4)
unnamed: D913.1 (K), IC902.14 (B4)
unnamed: D913.2 (A), RN902.6 (R5)
unnamed: D914.1 (K), IC902.13 (B5)
unnamed: D914.2 (A), RN902.7 (R6)
unnamed: D915.1 (K), IC902.12 (B6)
unnamed: D915.2 (A), RN902.8 (R7)
unnamed: D916.1 (K), IC902.11 (B7)
unnamed: D916.2 (A), RN902.9 (R8)

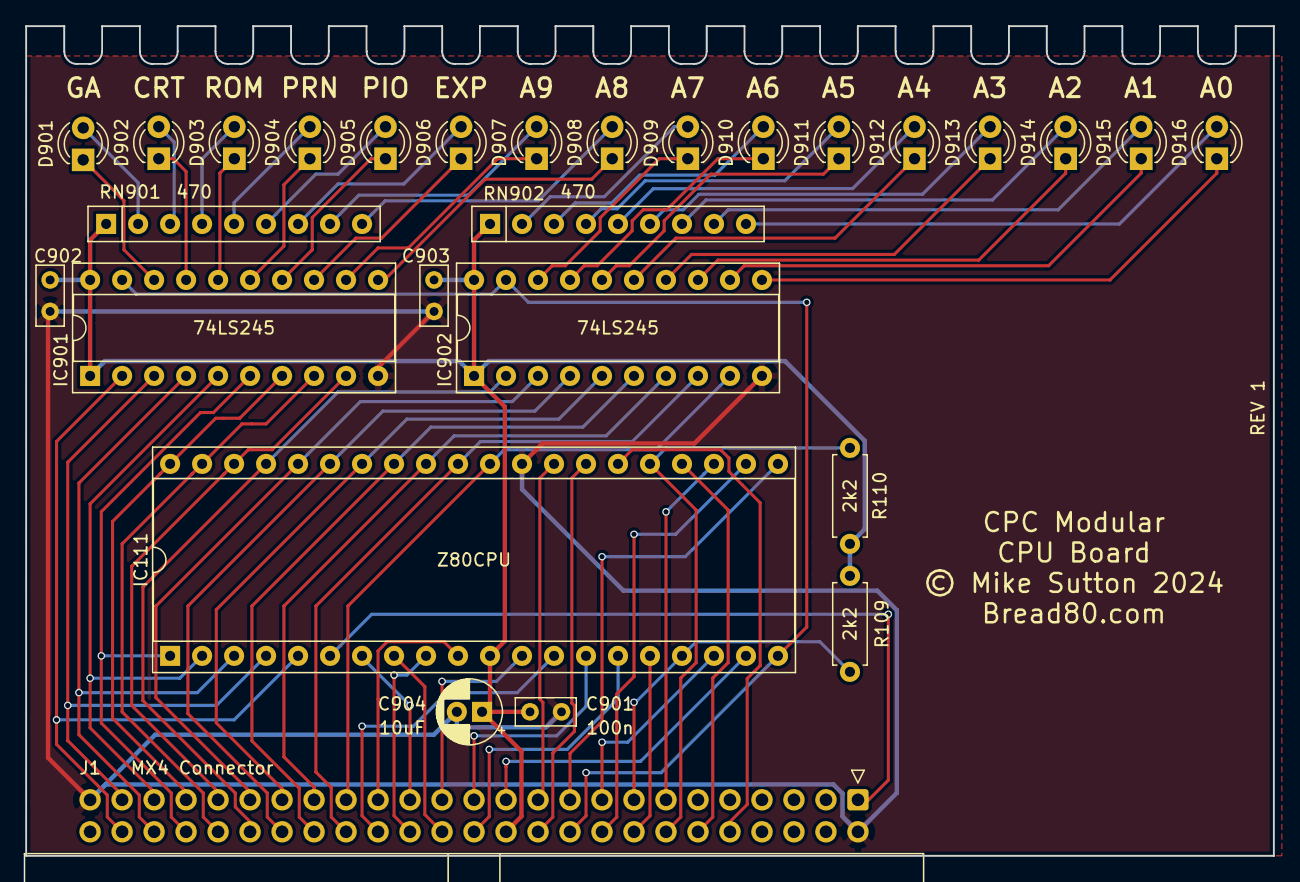
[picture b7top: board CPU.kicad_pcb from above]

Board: 2 copper layers, 99.1 x 65.9 mm, 28 parts (0 on the bottom side), 72 nets.
